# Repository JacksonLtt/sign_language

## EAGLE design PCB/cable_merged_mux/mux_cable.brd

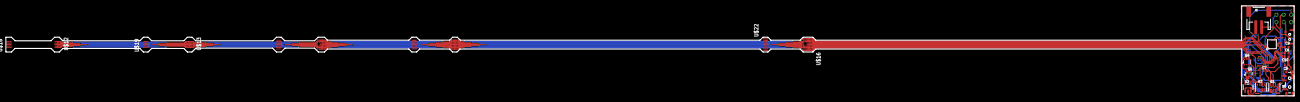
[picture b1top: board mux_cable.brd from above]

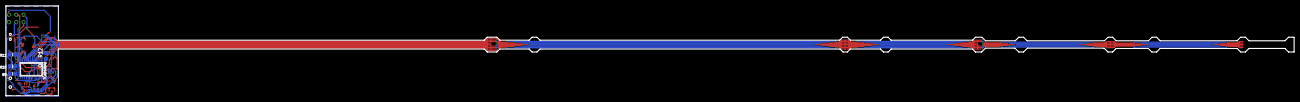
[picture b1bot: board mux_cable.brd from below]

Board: 2 copper layers, 436.6 x 30.5 mm, 35 parts (5 on the bottom side), 23 nets.

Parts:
C5: 1uF; C0402
C6: 2.2uF; C0402
C7, C9: 0.1uF; C0402
C10: 10uF; C0402
J2: JST-2-SMD
Q1, Q4: BSS138; SOT363
R1: 10K; RESPACK_4X0603
R7: 4.7K; RESPACK_4X0603
R9, R10, R11: 10K; 0805-NO
R12: 10k; R0805
S1: SWITCH_SPST_SMD_A
TCA9448A1: MICROBUILDER_TSSOP24
U2: MIC5225-1.8V; SOT23-5
U$12, U$13, U$18, U$19: FPC050505; FPC0505
U$14, U$15, U$20, U$21: FPC070505; FPC0705
U$16, U$22: FPC090505; FPC0905
U$39: MPU-9250_ICM20948; QFN24_3MM_NOEP
U$58: 24*3.5; 2*4*3.5
U$59, U$60, U$61, U$62, U$63, U$64: M0.9-HOLE0.9MM; M0.9-HOLE

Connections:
1.8V: C6.1, C7.1, Q1.2, Q1.5, Q4.5, R1.4, R1.8, R7.8, U2.5, U$12.P$4, U$13.P$4, U$14.P$5, U$15.P$5, U$16.P$6, U$39.8, U$39.13
BATTERY: S1.2, U$62.P$1
BUTTON: U$58.P$4, U$61.P$1
GND: C5.2, C6.2, C7.2, C9.2, C10.2, J2.1, R9.2, R10.2, R11.2, S1.3, TCA9448A1.12, U2.2, U$12.P$1, U$13.P$1, U$14.P$2, U$15.P$2, U$16.P$3, U$39.18, U$39.20, U$58.P$3, U$60.P$1
unnamed: J2.2, S1.1
unnamed: R9.1, TCA9448A1.21
unnamed: R10.1, TCA9448A1.2
unnamed: R11.1, TCA9448A1.1
REGOUT1: C9.1, U$39.10
RESET1: R12.1, TCA9448A1.3
SCK/SCL_1.8V: Q1.4, R1.1, U$39.23
SCL: TCA9448A1.22, U$64.P$1
SCL1: Q1.3, R1.6, TCA9448A1.5, U$16.P$4
SCL2: TCA9448A1.7, U$14.P$3, U$15.P$3, U$16.P$2
SCL3: TCA9448A1.9, U$12.P$2, U$13.P$2, U$14.P$1, U$15.P$1, U$16.P$1
SDA: TCA9448A1.23, U$63.P$1
SDA1: Q1.6, R1.7, TCA9448A1.4, U$16.P$5
SDA2: TCA9448A1.6, U$14.P$4, U$15.P$4, U$16.P$8
SDA3: TCA9448A1.8, U$12.P$3, U$13.P$3, U$14.P$7, U$15.P$7, U$16.P$9
SDI/SDA_1.8V: Q1.1, R1.5, U$39.24
SDO/ADR1: Q4.3, R7.2
SDO/ADR_1.8V: Q4.4, R7.1, U$39.9
VIN: C5.1, C10.1, R1.2, R1.3, R7.7, R12.2, TCA9448A1.24, U2.1, U2.3, U$12.P$5, U$13.P$5, U$14.P$6, U$15.P$6, U$16.P$7, U$59.P$1

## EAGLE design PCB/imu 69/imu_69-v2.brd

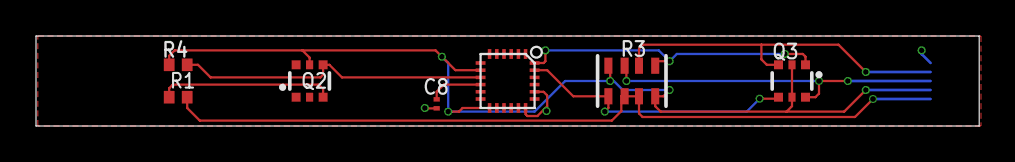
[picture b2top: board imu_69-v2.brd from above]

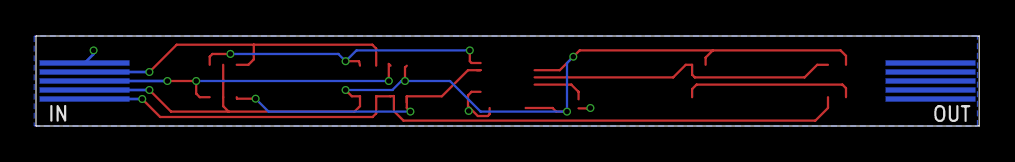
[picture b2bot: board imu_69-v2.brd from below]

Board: 2 copper layers, 52.4 x 5.0 mm, 9 parts (2 on the bottom side), 10 nets.

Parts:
C8: 0.1uF; C0201
Q2, Q3: BSS138; SOT363
R1, R4: 4.7k; R0402
R3: 10K; RESPACK_4X0603
U$1, U$2: FPC0510
U$21: MPU-9250_ICM20948; QFN24_3MM_NOEP

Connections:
1.8V: Q2.5, Q3.2, Q3.5, R3.4, R3.8, R4.2, U$1.P$2, U$21.8, U$21.13
GND: C8.2, U$1.P$5, U$21.18, U$21.20
REGOUT: C8.1, U$21.10
SCK/SCL: Q3.3, R3.6, U$1.P$4
SCK/SCL_1.8V: Q3.4, R3.1, U$21.23
SDI/SDA: Q3.6, R3.7, U$1.P$3
SDI/SDA_1.8V: Q3.1, R3.5, U$21.24
SDO/ADR: Q2.3, R1.1
SDO/ADR_1.8V: Q2.4, R4.1, U$21.9
VIN: R1.2, R3.2, R3.3, U$1.P$1

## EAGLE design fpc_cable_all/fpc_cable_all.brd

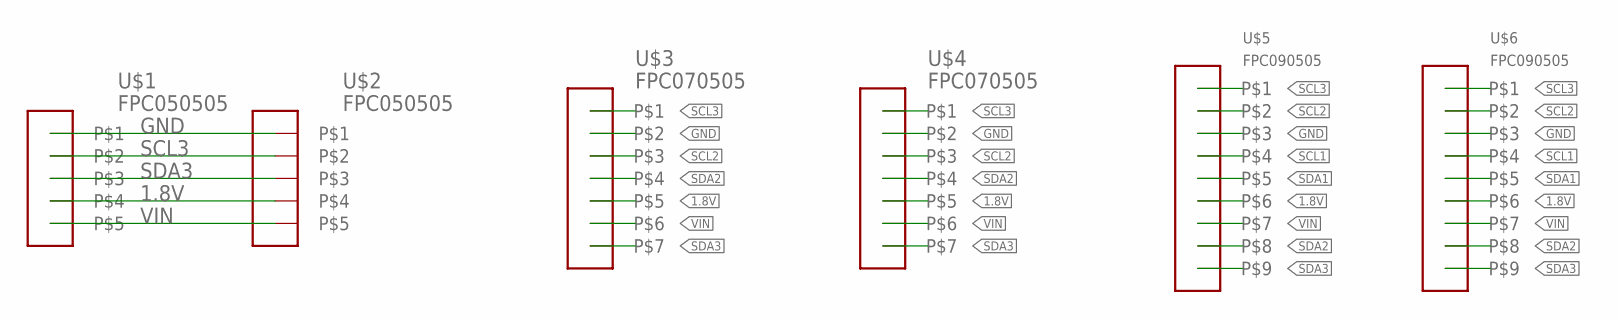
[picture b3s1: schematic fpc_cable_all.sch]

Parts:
U$1, U$2: FPC050505; FPC0505
U$3, U$4: FPC070505; FPC0705
U$5, U$6: FPC090505; FPC0905

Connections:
1.8V: U$1.P$4, U$2.P$4, U$3.P$5, U$4.P$5, U$5.P$6, U$6.P$6
GND: U$1.P$1, U$2.P$1, U$3.P$2, U$4.P$2, U$5.P$3, U$6.P$3
SCL1: U$5.P$4, U$6.P$4
SCL2: U$3.P$3, U$4.P$3, U$5.P$2, U$6.P$2
SCL3: U$1.P$2, U$2.P$2, U$3.P$1, U$4.P$1, U$5.P$1, U$6.P$1
SDA1: U$5.P$5, U$6.P$5
SDA2: U$3.P$4, U$4.P$4, U$5.P$8, U$6.P$8
SDA3: U$1.P$3, U$2.P$3, U$3.P$7, U$4.P$7, U$5.P$9, U$6.P$9
VIN: U$1.P$5, U$2.P$5, U$3.P$6, U$4.P$6, U$5.P$7, U$6.P$7

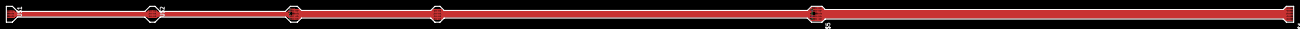
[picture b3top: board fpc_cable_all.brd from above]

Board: 2 copper layers, 406.1 x 5.0 mm, 6 parts (0 on the bottom side), 9 nets.

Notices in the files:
parts and their libraries:
microbuilder: This work is placed in the public domain, and may be freely used for commercial and non-commercial work with the following conditions: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
SparkFun-Connectors: Licensing: Creative Commons ShareAlike 4.0 International - https://creativecommons.org/licenses/by-sa/4.0
